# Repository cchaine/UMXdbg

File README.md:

# UMXdbg
A Hardware Debugger board to test UMXbus modules independently

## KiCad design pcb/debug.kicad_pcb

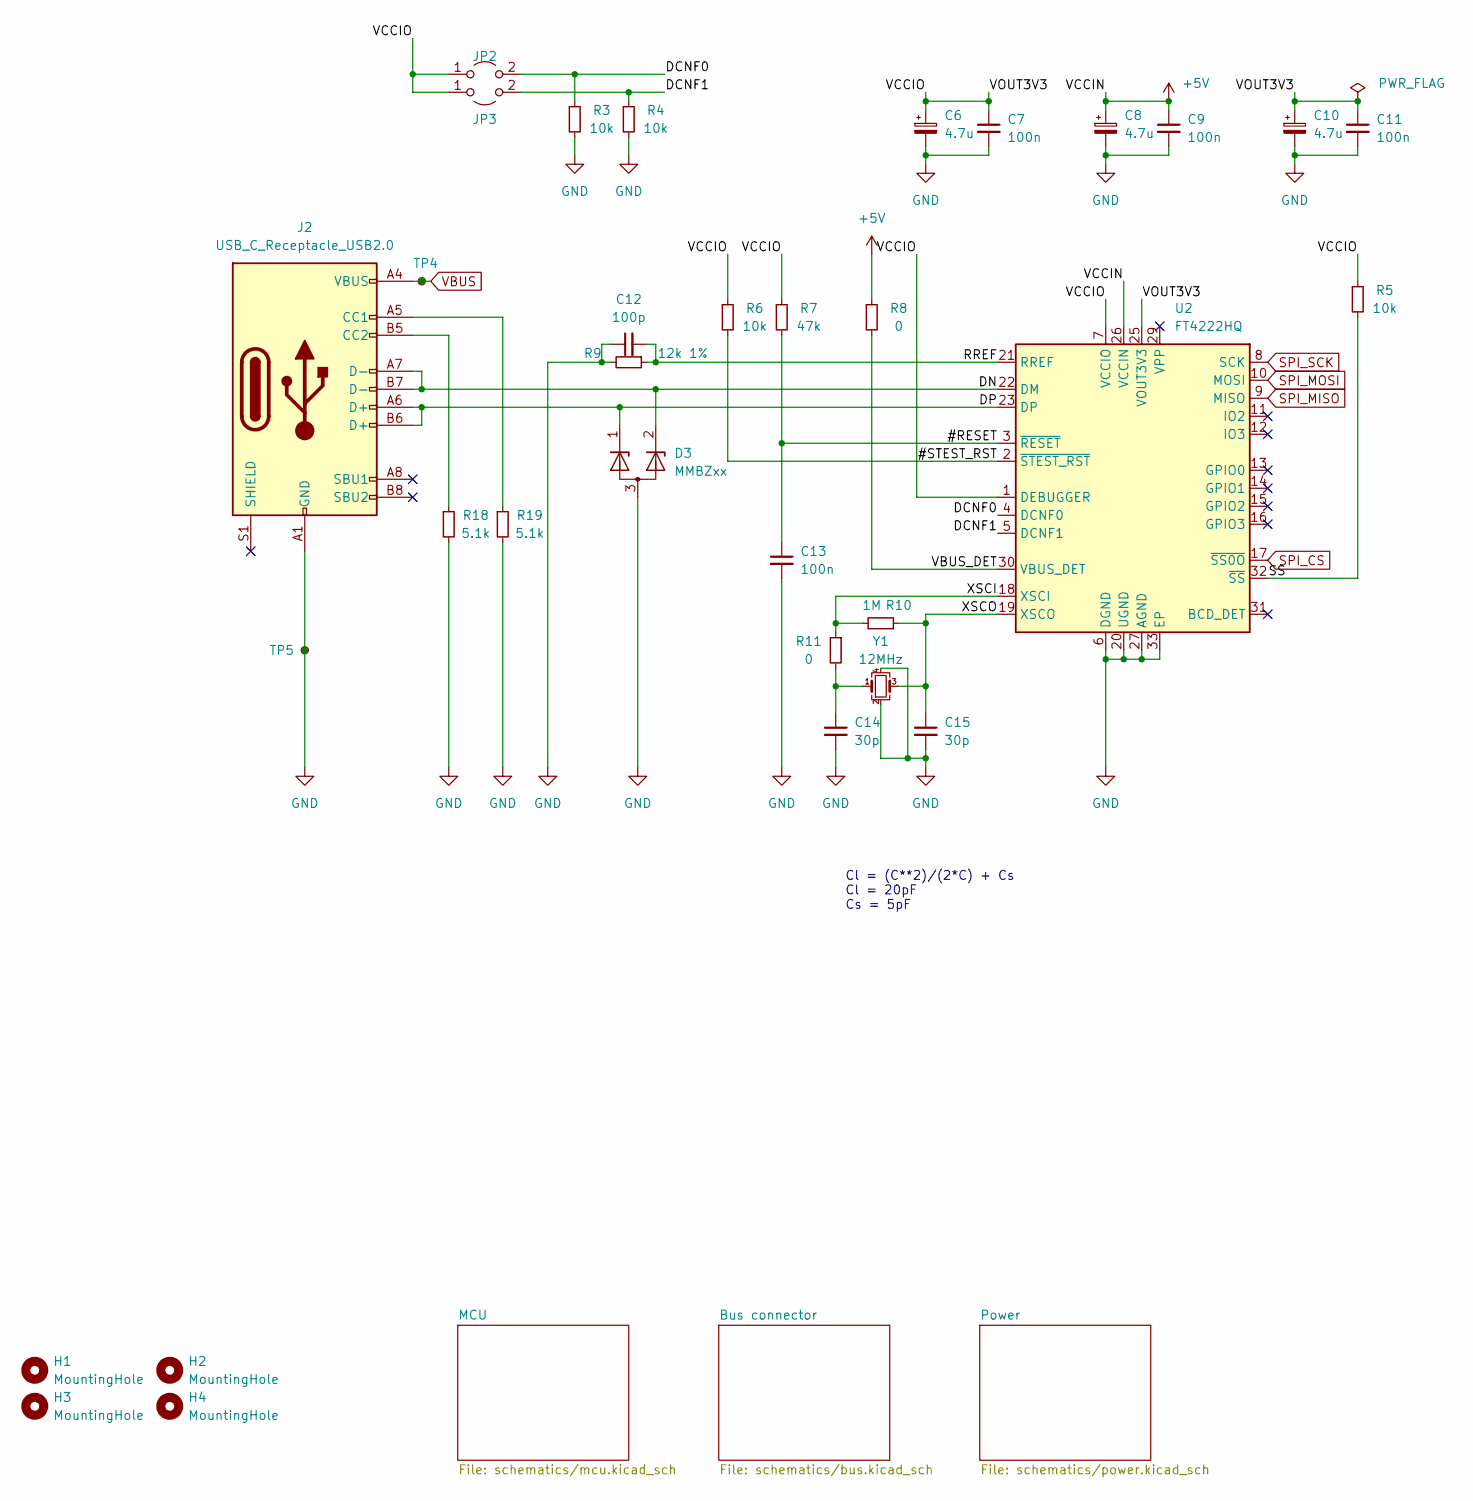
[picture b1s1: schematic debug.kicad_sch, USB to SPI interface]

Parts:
C6, C8, C10: 4.7u; C_0805_2012Metric; Part Number GRM21BR71C475KE51L
C7, C9, C11, C13: 100n; C_0603_1608Metric; Part Number 885012206095
C12: 100p; C_0603_1608Metric; Part Number 06035A101JAT4A
C14, C15: 30p; C_0603_1608Metric; Part Number C0603C300K1HACTU
D3: MMBZxx; SOT-23; Part Number MMBZ5V6ALFHT116
H1, H2, H3, H4: MountingHole; MountingHole_2.7mm_M2.5
J2: USB_C_Receptacle_USB2.0; GCT_USB4105-GF-A; Part Number USB4105-GF-A
JP2, JP3: Jumper_2_Open; SolderJumper-2_P1.3mm_Open_RoundedPad1.0x1.5mm
R3, R4, R5, R6: 10k; R_0603_1608Metric; Part Number CR0603-FX-1002ELF
R7: 47k; R_0603_1608Metric; Part Number AC0603FR-0747KL
R8, R11: 0; R_0603_1608Metric; Part Number CR0603-J/-000ELF
R9: 12k 1%; R_0603_1608Metric; Part Number RC0603FR-1012KL
R10: 1M; R_0603_1608Metric; Part Number CR0603-FX-1004ELF
R18, R19: 5.1k; R_0603_1608Metric; Part Number CR0603-FX-5101ELF
TP4, TP5: TestPoint_Small; TestPoint_Loop_D2.54mm_Drill1.5mm_Beaded
U2: FT4222HQ; VQFN-32-1EP_5x5mm_P0.5mm_EP3.1x3.1mm; Part Number FT4222HQ-D-R
Y1: 12MHz; XTAL_ECS-120-18-33-JGN-TR; Part Number ECS-120-18-33-JGN-TR3

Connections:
+5V: C8.1, C9.1, R8.1, U2.26 (VCCIN); also elsewhere on the board
/#RESET: C13.1, R7.2, U2.3 (~RESET)
/#STEST_RST: R6.2, U2.2 (~STEST_RST)
/DCNF0: JP2.2 (B), R3.1, U2.4 (DCNF0)
/DCNF1: JP3.2 (B), R4.1, U2.5 (DCNF1)
/DN: D3.2 (K), J2.A7 (D-), J2.B7 (D-), U2.22 (DM)
/DP: D3.1 (K), J2.A6 (D+), J2.B6 (D+), U2.23 (DP)
/RREF: C12.2, R9.1, U2.21 (RREF)
/SS: R5.2, U2.32 (~SS)
/VBUS_DET: R8.2, U2.30 (VBUS_DET)
/VCCIO: C6.1, C7.1, C10.1, C11.1, JP2.1 (A), JP3.1 (A), R5.1, R6.1, R7.1, U2.1 (DEBUGGER), U2.7 (VCCIO), U2.25 (VOUT3V3)
/XSCI: R10.2, R11.1, U2.18 (XSCI)
/XSCO: C15.1, R10.1, U2.19 (XSCO), Y1.3
GND: C6.2, C7.2, C8.2, C9.2, C10.2, C11.2, C12.1, C13.2, C14.2, C15.2, D3.3 (A), J2.A1 (GND), J2.A12 (GND), J2.B1 (GND), J2.B12 (GND), R3.2, R4.2, R9.2, R18.2, R19.2, TP5.1, U2.6 (DGND), U2.20 (UGND), U2.24 (UGND), U2.27 (AGND), U2.28 (DGND), U2.33 (EP), Y1.2, Y1.4; also elsewhere on the board
unnamed: C14.1, R11.2, Y1.1
unnamed: J2.A5 (CC1), R19.1
unnamed: J2.B5 (CC2), R18.1
SPI_CS: U2.17 (~SS0O); also elsewhere on the board
SPI_MISO: U2.9 (MISO); also elsewhere on the board
SPI_MOSI: U2.10 (MOSI); also elsewhere on the board
SPI_SCK: U2.8 (SCK); also elsewhere on the board
VBUS: J2.A4 (VBUS), J2.A9 (VBUS), J2.B4 (VBUS), J2.B9 (VBUS), TP4.1; also elsewhere on the board

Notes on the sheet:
Cl = (C**2)/(2*C) + Cs Cl = 20pF Cs = 5pF

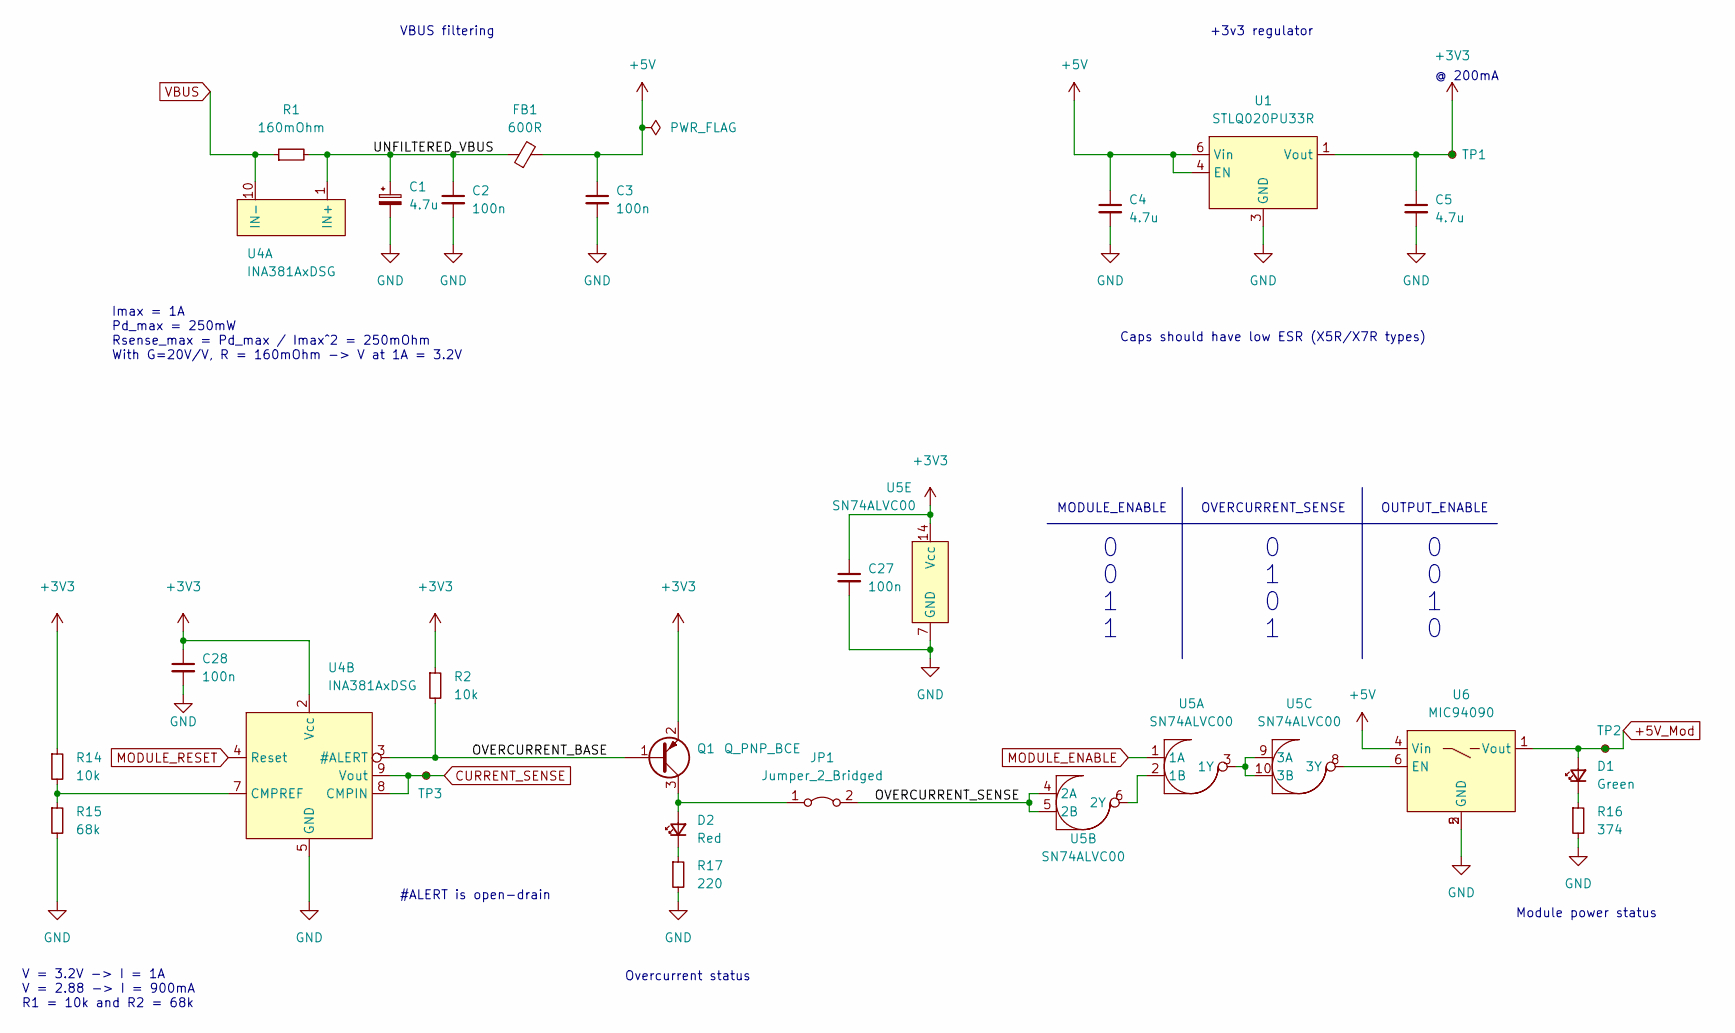
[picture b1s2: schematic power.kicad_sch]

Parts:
C1, C4, C5: 4.7u; C_0805_2012Metric; Part Number GRM21BR71C475KE51L
C2, C3, C27, C28: 100n; C_0603_1608Metric; Part Number 885012206095
D1: Green; LED_1206_3216Metric; Part Number 156120VS75300
D2: Red; LED_1206_3216Metric; Part Number 156120RS75300
FB1: 600R; L_1206_3216Metric; Part Number MH3261-601Y
JP1: Jumper_2_Bridged; SolderJumper-2_P1.3mm_Bridged_RoundedPad1.0x1.5mm
Q1: Q_PNP_BCE; SOT-23; Part Number BC857,215
R1: 160mOhm; R_0805_2012Metric; Part Number RL1220S-R16-F
R2, R14: 10k; R_0603_1608Metric; Part Number CR0603-FX-1002ELF
R15: 68k; R_0603_1608Metric; Part Number CR0603-FX-6802ELF
R16: 374; R_0603_1608Metric; Part Number CR0603-FX-3740ELF
R17: 220; R_0603_1608Metric; Part Number RC0603FR-07220RL
TP1, TP2, TP3: TestPoint_Small; TestPoint_Loop_D2.54mm_Drill1.5mm_Beaded
U1: STLQ020PU33R; DFN-6-1EP_2x2mm_P0.5mm_EP0.6x1.37mm; Part Number STLQ020PU33R
U4: INA381AxDSG; VSSOP-10_3x3mm_P0.5mm; Part Number INA381A1IDGSR
U5: SN74ALVC00; TSSOP-14_4.4x5mm_P0.65mm; Part Number SN74ALVC00PWR
U6: MIC94090; SOT-363_SC-70-6; Part Number MIC94090YC6-TR

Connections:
+3V3: C5.1, C27.1, C28.1, Q1.2 (E), R2.1, R14.1, TP1.1, U1.1 (Vout), U4.2 (Vcc), U5.14 (Vcc); also elsewhere on the board
+5V: C3.1, C4.1, FB1.2, U1.4 (EN), U1.6 (Vin), U6.4 (Vin); also elsewhere on the board
+5V_Mod: D1.2 (A), TP2.1, U6.1 (Vout); also elsewhere on the board
/Power/OVERCURRENT_BASE: Q1.1 (B), R2.2, U4.3 (#ALERT)
/Power/OVERCURRENT_SENSE: JP1.2 (B), U5.4 (2A), U5.5 (2B)
/Power/UNFILTERED_VBUS: C1.1, C2.1, FB1.1, R1.2, U4.1 (IN+)
CURRENT_SENSE: TP3.1, U4.8 (CMPIN), U4.9 (Vout); also elsewhere on the board
GND: C1.2, C2.2, C3.2, C4.2, C5.2, C27.2, C28.2, R15.2, R16.2, R17.2, U1.3 (GND), U4.5 (GND), U5.7 (GND), U6.2 (GND), U6.5 (GND); also elsewhere on the board
MODULE_ENABLE: U5.1 (1A); also elsewhere on the board
MODULE_RESET: U4.4 (Reset); also elsewhere on the board
unnamed: D1.1 (K), R16.1
unnamed: D2.2 (A), JP1.1 (A), Q1.3 (C)
unnamed: D2.1 (K), R17.1
unnamed: R14.2, R15.1, U4.7 (CMPREF)
unnamed: U5.2 (1B), U5.6 (2Y)
unnamed: U5.3 (1Y), U5.9 (3A), U5.10 (3B)
unnamed: U5.8 (3Y), U6.6 (EN)
VBUS: R1.1, U4.10 (IN-); also elsewhere on the board

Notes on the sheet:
OVERCURRENT_SENSE
Module power status
Overcurrent status
@ 200mA
VBUS filtering
V = 3.2V -> I = 1A V = 2.88 -> I = 900mA R1 = 10k and R2 = 68k
Imax = 1A Pd_max = 250mW Rsense_max = Pd_max / Imax^2 = 250mOhm With G=20V/V, R = 160mOhm -> V at 1A = 3.2V
+3v3 regulator
#ALERT is open-drain
OUTPUT_ENABLE
Caps should have low ESR (X5R/X7R types)
MODULE_ENABLE

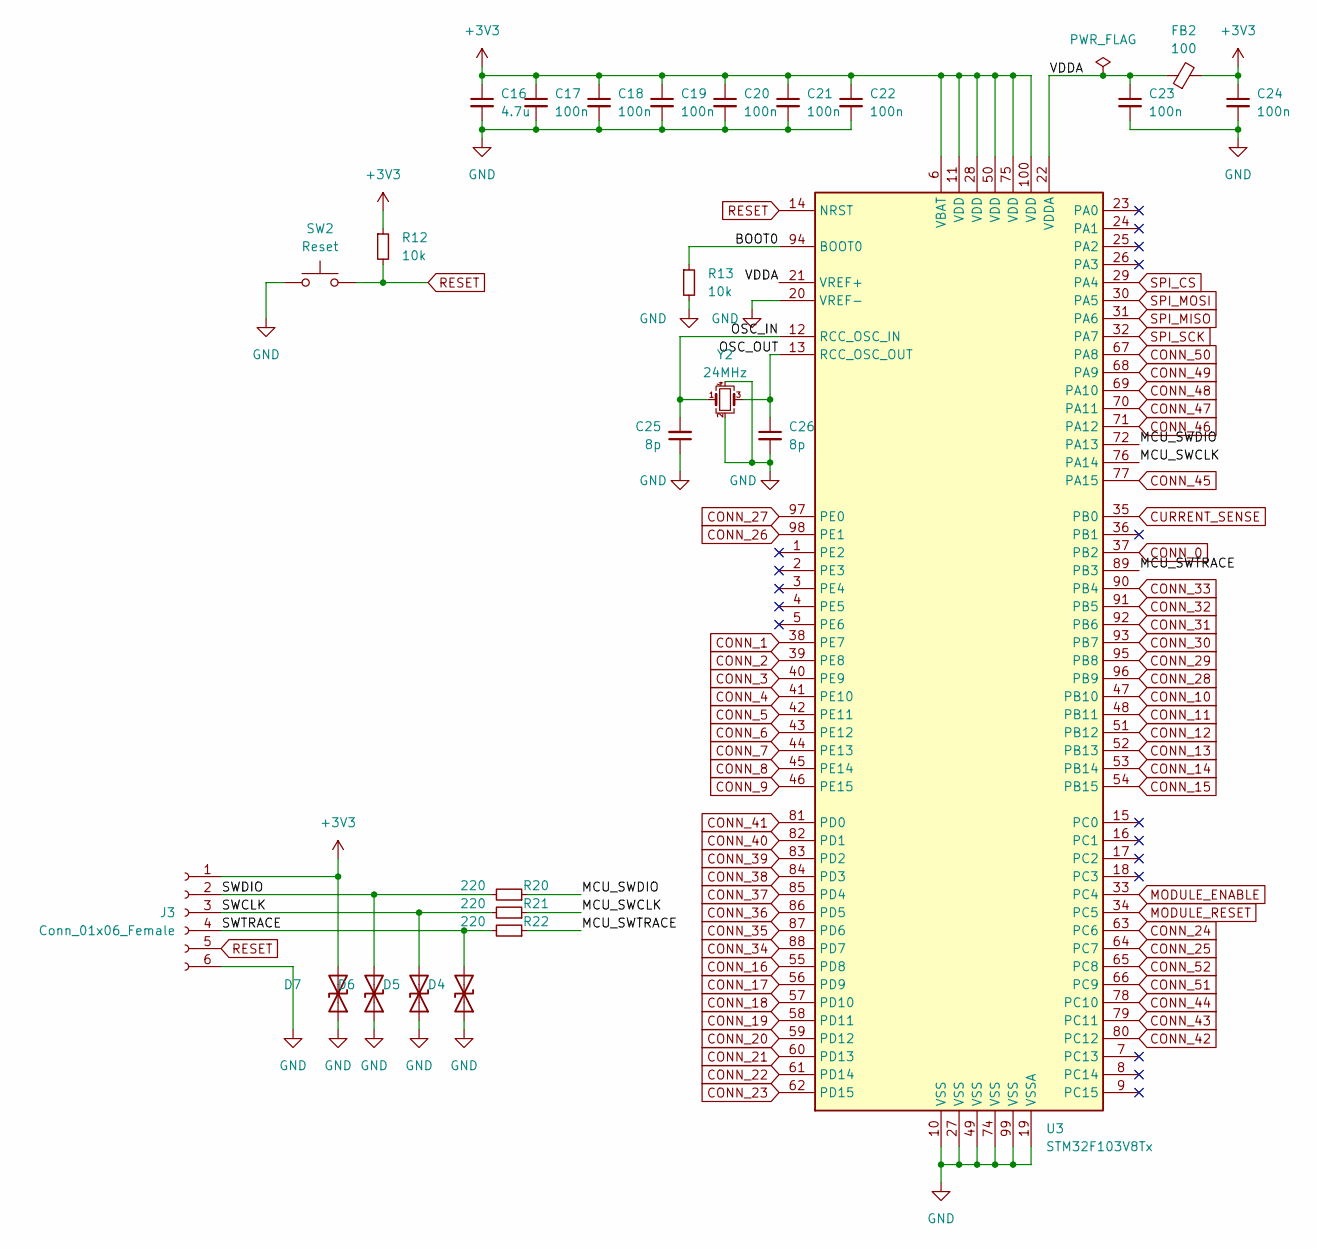
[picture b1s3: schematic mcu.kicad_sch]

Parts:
C16: 4.7u; C_0805_2012Metric; Part Number GRM21BR71C475KE51L
C17, C18, C19, C20, C21, C22, C23, C24: 100n; C_0603_1608Metric; Part Number 885012206095
C25, C26: 8p; C_0603_1608Metric; Part Number C1608C0G1H080D080AA
D4, D5, D6, D7: D_TVS; TVS_ESD9D5.0ST5G; Part Number DF2S10FS,L3M
FB2: 100; L_0805_2012Metric; Part Number MG2029-101Y
J3: Conn_01x06_Female; PinHeader_1x06_P1.27mm_Vertical
R12, R13: 10k; R_0603_1608Metric; Part Number CR0603-FX-1002ELF
R20, R21, R22: 220; R_0603_1608Metric; Part Number RC0603FR-07220RL
SW2: Reset; Panasonic_EVQPUJ_EVQPUA
U3: STM32F103V8Tx; LQFP-100_14x14mm_P0.5mm; Part Number STM32F103V8Tx
Y2: 24MHz; Crystal_SMD_SeikoEpson_TSX3225-4Pin_3.2x2.5mm; Part Number 732-22524MF15X-AC6

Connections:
+3V3: C16.1, C17.1, C18.1, C19.1, C20.1, C21.1, C22.1, C24.1, D7.2 (A2), FB2.2, J3.1, R12.1, U3.6 (VBAT), U3.11 (VDD), U3.28 (VDD), U3.50 (VDD), U3.75 (VDD), U3.100 (VDD); also elsewhere on the board
/MCU/BOOT0: R13.1, U3.94 (BOOT0)
/MCU/MCU_SWCLK: R21.1, U3.76 (PA14)
/MCU/MCU_SWDIO: R20.1, U3.72 (PA13)
/MCU/MCU_SWTRACE: R22.1, U3.89 (PB3)
/MCU/OSC_IN: C25.2, U3.12 (RCC_OSC_IN), Y2.1
/MCU/OSC_OUT: C26.1, U3.13 (RCC_OSC_OUT), Y2.3
/MCU/SWCLK: D5.2 (A2), J3.3, R21.2
/MCU/SWDIO: D6.2 (A2), J3.2, R20.2
/MCU/SWTRACE: D4.2 (A2), J3.4, R22.2
/MCU/VDDA: C23.1, FB2.1, U3.21 (VREF+), U3.22 (VDDA)
CONN_0: U3.37 (PB2); also elsewhere on the board
CONN_1: U3.38 (PE7); also elsewhere on the board
CONN_2: U3.39 (PE8); also elsewhere on the board
CONN_3: U3.40 (PE9); also elsewhere on the board
CONN_4: U3.41 (PE10); also elsewhere on the board
CONN_5: U3.42 (PE11); also elsewhere on the board
CONN_6: U3.43 (PE12); also elsewhere on the board
CONN_7: U3.44 (PE13); also elsewhere on the board
CONN_8: U3.45 (PE14); also elsewhere on the board
CONN_9: U3.46 (PE15); also elsewhere on the board
CONN_10: U3.47 (PB10); also elsewhere on the board
CONN_11: U3.48 (PB11); also elsewhere on the board
CONN_12: U3.51 (PB12); also elsewhere on the board
CONN_13: U3.52 (PB13); also elsewhere on the board
CONN_14: U3.53 (PB14); also elsewhere on the board
CONN_15: U3.54 (PB15); also elsewhere on the board
CONN_16: U3.55 (PD8); also elsewhere on the board
CONN_17: U3.56 (PD9); also elsewhere on the board
CONN_18: U3.57 (PD10); also elsewhere on the board
CONN_19: U3.58 (PD11); also elsewhere on the board
CONN_20: U3.59 (PD12); also elsewhere on the board
CONN_21: U3.60 (PD13); also elsewhere on the board
CONN_22: U3.61 (PD14); also elsewhere on the board
CONN_23: U3.62 (PD15); also elsewhere on the board
CONN_24: U3.63 (PC6); also elsewhere on the board
CONN_25: U3.64 (PC7); also elsewhere on the board
CONN_26: U3.98 (PE1); also elsewhere on the board
CONN_27: U3.97 (PE0); also elsewhere on the board
CONN_28: U3.96 (PB9); also elsewhere on the board
CONN_29: U3.95 (PB8); also elsewhere on the board
CONN_30: U3.93 (PB7); also elsewhere on the board
CONN_31: U3.92 (PB6); also elsewhere on the board
CONN_32: U3.91 (PB5); also elsewhere on the board
CONN_33: U3.90 (PB4); also elsewhere on the board
CONN_34: U3.88 (PD7); also elsewhere on the board
CONN_35: U3.87 (PD6); also elsewhere on the board
CONN_36: U3.86 (PD5); also elsewhere on the board
CONN_37: U3.85 (PD4); also elsewhere on the board
CONN_38: U3.84 (PD3); also elsewhere on the board
CONN_39: U3.83 (PD2); also elsewhere on the board
CONN_40: U3.82 (PD1); also elsewhere on the board
CONN_41: U3.81 (PD0); also elsewhere on the board
CONN_42: U3.80 (PC12); also elsewhere on the board
CONN_43: U3.79 (PC11); also elsewhere on the board
CONN_44: U3.78 (PC10); also elsewhere on the board
CONN_45: U3.77 (PA15); also elsewhere on the board
CONN_46: U3.71 (PA12); also elsewhere on the board
CONN_47: U3.70 (PA11); also elsewhere on the board
CONN_48: U3.69 (PA10); also elsewhere on the board
CONN_49: U3.68 (PA9); also elsewhere on the board
CONN_50: U3.67 (PA8); also elsewhere on the board
CONN_51: U3.66 (PC9); also elsewhere on the board
CONN_52: U3.65 (PC8); also elsewhere on the board
CURRENT_SENSE: U3.35 (PB0); also elsewhere on the board
GND: C16.2, C17.2, C18.2, C19.2, C20.2, C21.2, C22.2, C23.2, C24.2, C25.1, C26.2, D4.1 (A1), D5.1 (A1), D6.1 (A1), D7.1 (A1), J3.6, R13.2, SW2.1, U3.10 (VSS), U3.19 (VSSA), U3.20 (VREF-), U3.27 (VSS), U3.49 (VSS), U3.74 (VSS), U3.99 (VSS), Y2.2, Y2.4; also elsewhere on the board
MODULE_ENABLE: U3.33 (PC4); also elsewhere on the board
MODULE_RESET: U3.34 (PC5); also elsewhere on the board
RESET: J3.5, R12.2, SW2.2, U3.14 (NRST)
SPI_CS: U3.29 (PA4); also elsewhere on the board
SPI_MISO: U3.31 (PA6); also elsewhere on the board
SPI_MOSI: U3.30 (PA5); also elsewhere on the board
SPI_SCK: U3.32 (PA7); also elsewhere on the board

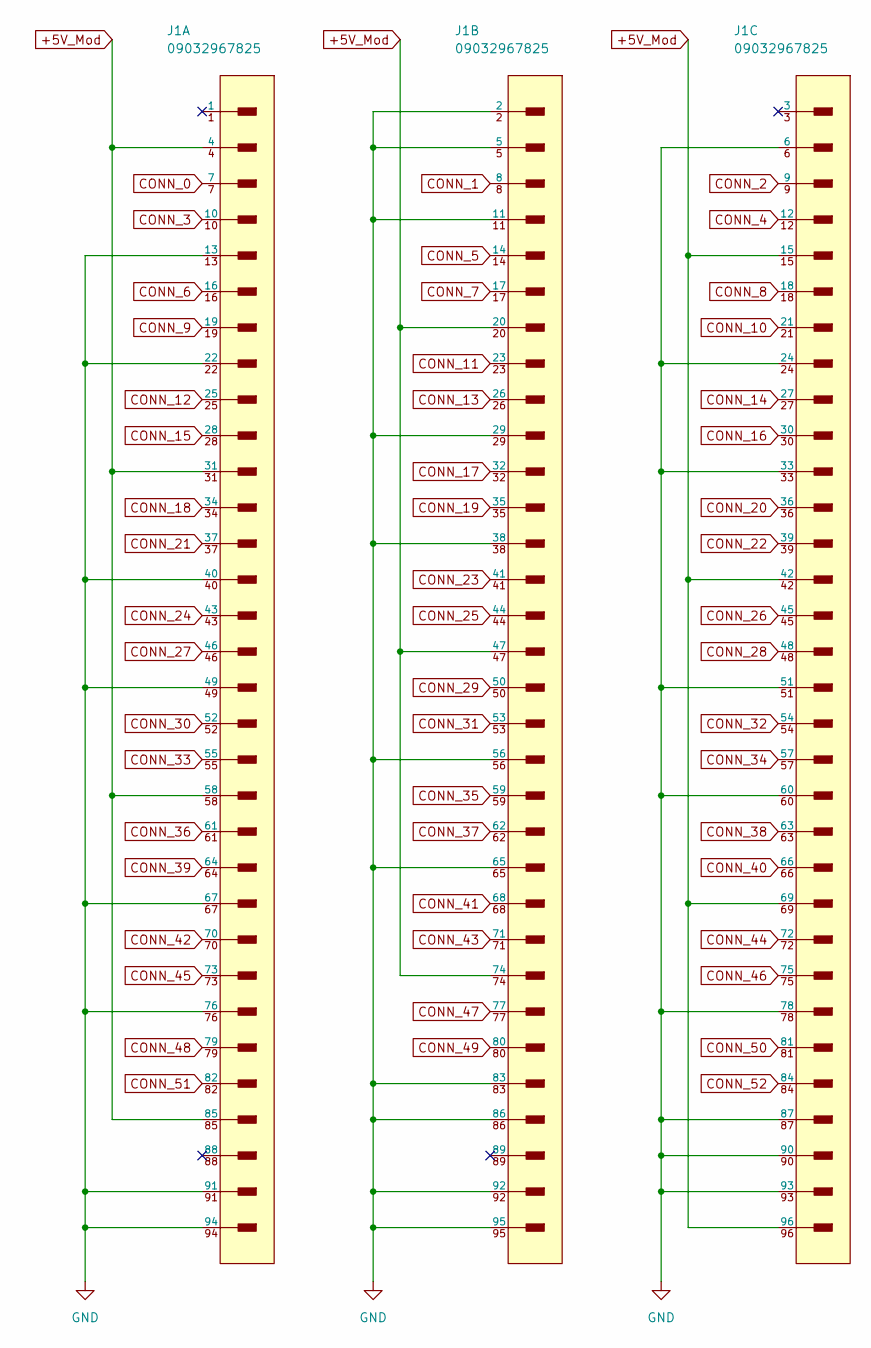
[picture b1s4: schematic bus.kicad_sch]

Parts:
J1: 09032967825; Harting-09031966921-0-0-0; current rating 2A; mouser part number 617-09-03-196-6921; digikey description DIN-SIGNAL C096MS-3,0C1-2

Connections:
+5V_Mod: J1.4, J1.15, J1.20, J1.31, J1.42, J1.47, J1.58, J1.69, J1.74, J1.85, J1.96; also elsewhere on the board
CONN_0: J1.7; also elsewhere on the board
CONN_1: J1.8; also elsewhere on the board
CONN_2: J1.9; also elsewhere on the board
CONN_3: J1.10; also elsewhere on the board
CONN_4: J1.12; also elsewhere on the board
CONN_5: J1.14; also elsewhere on the board
CONN_6: J1.16; also elsewhere on the board
CONN_7: J1.17; also elsewhere on the board
CONN_8: J1.18; also elsewhere on the board
CONN_9: J1.19; also elsewhere on the board
CONN_10: J1.21; also elsewhere on the board
CONN_11: J1.23; also elsewhere on the board
CONN_12: J1.25; also elsewhere on the board
CONN_13: J1.26; also elsewhere on the board
CONN_14: J1.27; also elsewhere on the board
CONN_15: J1.28; also elsewhere on the board
CONN_16: J1.30; also elsewhere on the board
CONN_17: J1.32; also elsewhere on the board
CONN_18: J1.34; also elsewhere on the board
CONN_19: J1.35; also elsewhere on the board
CONN_20: J1.36; also elsewhere on the board
CONN_21: J1.37; also elsewhere on the board
CONN_22: J1.39; also elsewhere on the board
CONN_23: J1.41; also elsewhere on the board
CONN_24: J1.43; also elsewhere on the board
CONN_25: J1.44; also elsewhere on the board
CONN_26: J1.45; also elsewhere on the board
CONN_27: J1.46; also elsewhere on the board
CONN_28: J1.48; also elsewhere on the board
CONN_29: J1.50; also elsewhere on the board
CONN_30: J1.52; also elsewhere on the board
CONN_31: J1.53; also elsewhere on the board
CONN_32: J1.54; also elsewhere on the board
CONN_33: J1.55; also elsewhere on the board
CONN_34: J1.57; also elsewhere on the board
CONN_35: J1.59; also elsewhere on the board
CONN_36: J1.61; also elsewhere on the board
CONN_37: J1.62; also elsewhere on the board
CONN_38: J1.63; also elsewhere on the board
CONN_39: J1.64; also elsewhere on the board
CONN_40: J1.66; also elsewhere on the board
CONN_41: J1.68; also elsewhere on the board
CONN_42: J1.70; also elsewhere on the board
CONN_43: J1.71; also elsewhere on the board
CONN_44: J1.72; also elsewhere on the board
CONN_45: J1.73; also elsewhere on the board
CONN_46: J1.75; also elsewhere on the board
CONN_47: J1.77; also elsewhere on the board
CONN_48: J1.79; also elsewhere on the board
CONN_49: J1.80; also elsewhere on the board
CONN_50: J1.81; also elsewhere on the board
CONN_51: J1.82; also elsewhere on the board
CONN_52: J1.84; also elsewhere on the board
GND: J1.2, J1.5, J1.6, J1.11, J1.13, J1.22, J1.24, J1.29, J1.33, J1.38, J1.40, J1.49, J1.51, J1.56, J1.60, J1.65, J1.67, J1.76, J1.78, J1.83, J1.86, J1.87, J1.90, J1.91, J1.92, J1.93, J1.94, J1.95; also elsewhere on the board

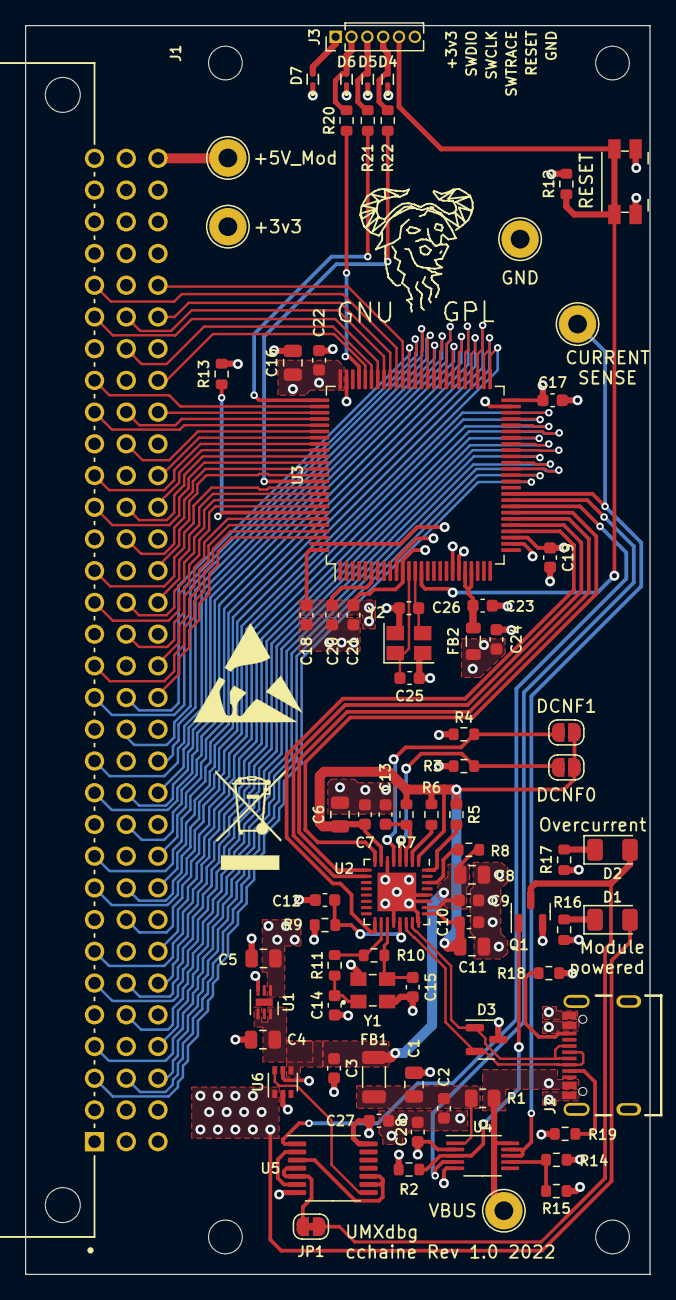
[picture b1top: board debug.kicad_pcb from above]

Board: 4 copper layers, 50.0 x 100.0 mm, 84 parts (0 on the bottom side), 101 nets.

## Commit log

2022-01-21 add main components
2022-01-21 add power schematics
2022-01-21 start the schematics for the usb to spi interface
2022-01-24 start choosing components, need to add overcurren t protection
2022-01-26 add current sensing
2022-01-26 add power switch simulation
2022-01-31 finish the schematic
2022-01-31 add components to the pcb
2022-01-31 start placing components
2022-02-01 moved components
2022-02-01 move components
2022-02-04 finished placing components
2022-02-04 route the power supply
2022-02-05 add missing 3d models
2022-02-06 route more components
2022-02-08 add SWD
2022-02-08 add bus traces
2022-02-11 add traces to the internal bus
2022-02-14 route more data traces
2022-02-15 finished routing the bus traces
2022-02-16 add power vias
2022-02-18 routed everything, need to add TP
2022-02-19 finished pcb
2022-05-28 finished the board
